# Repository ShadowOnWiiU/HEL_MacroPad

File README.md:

# HEL_MacroPad

## Macro Pad der 4AHEL Werkstaette

Current Look:

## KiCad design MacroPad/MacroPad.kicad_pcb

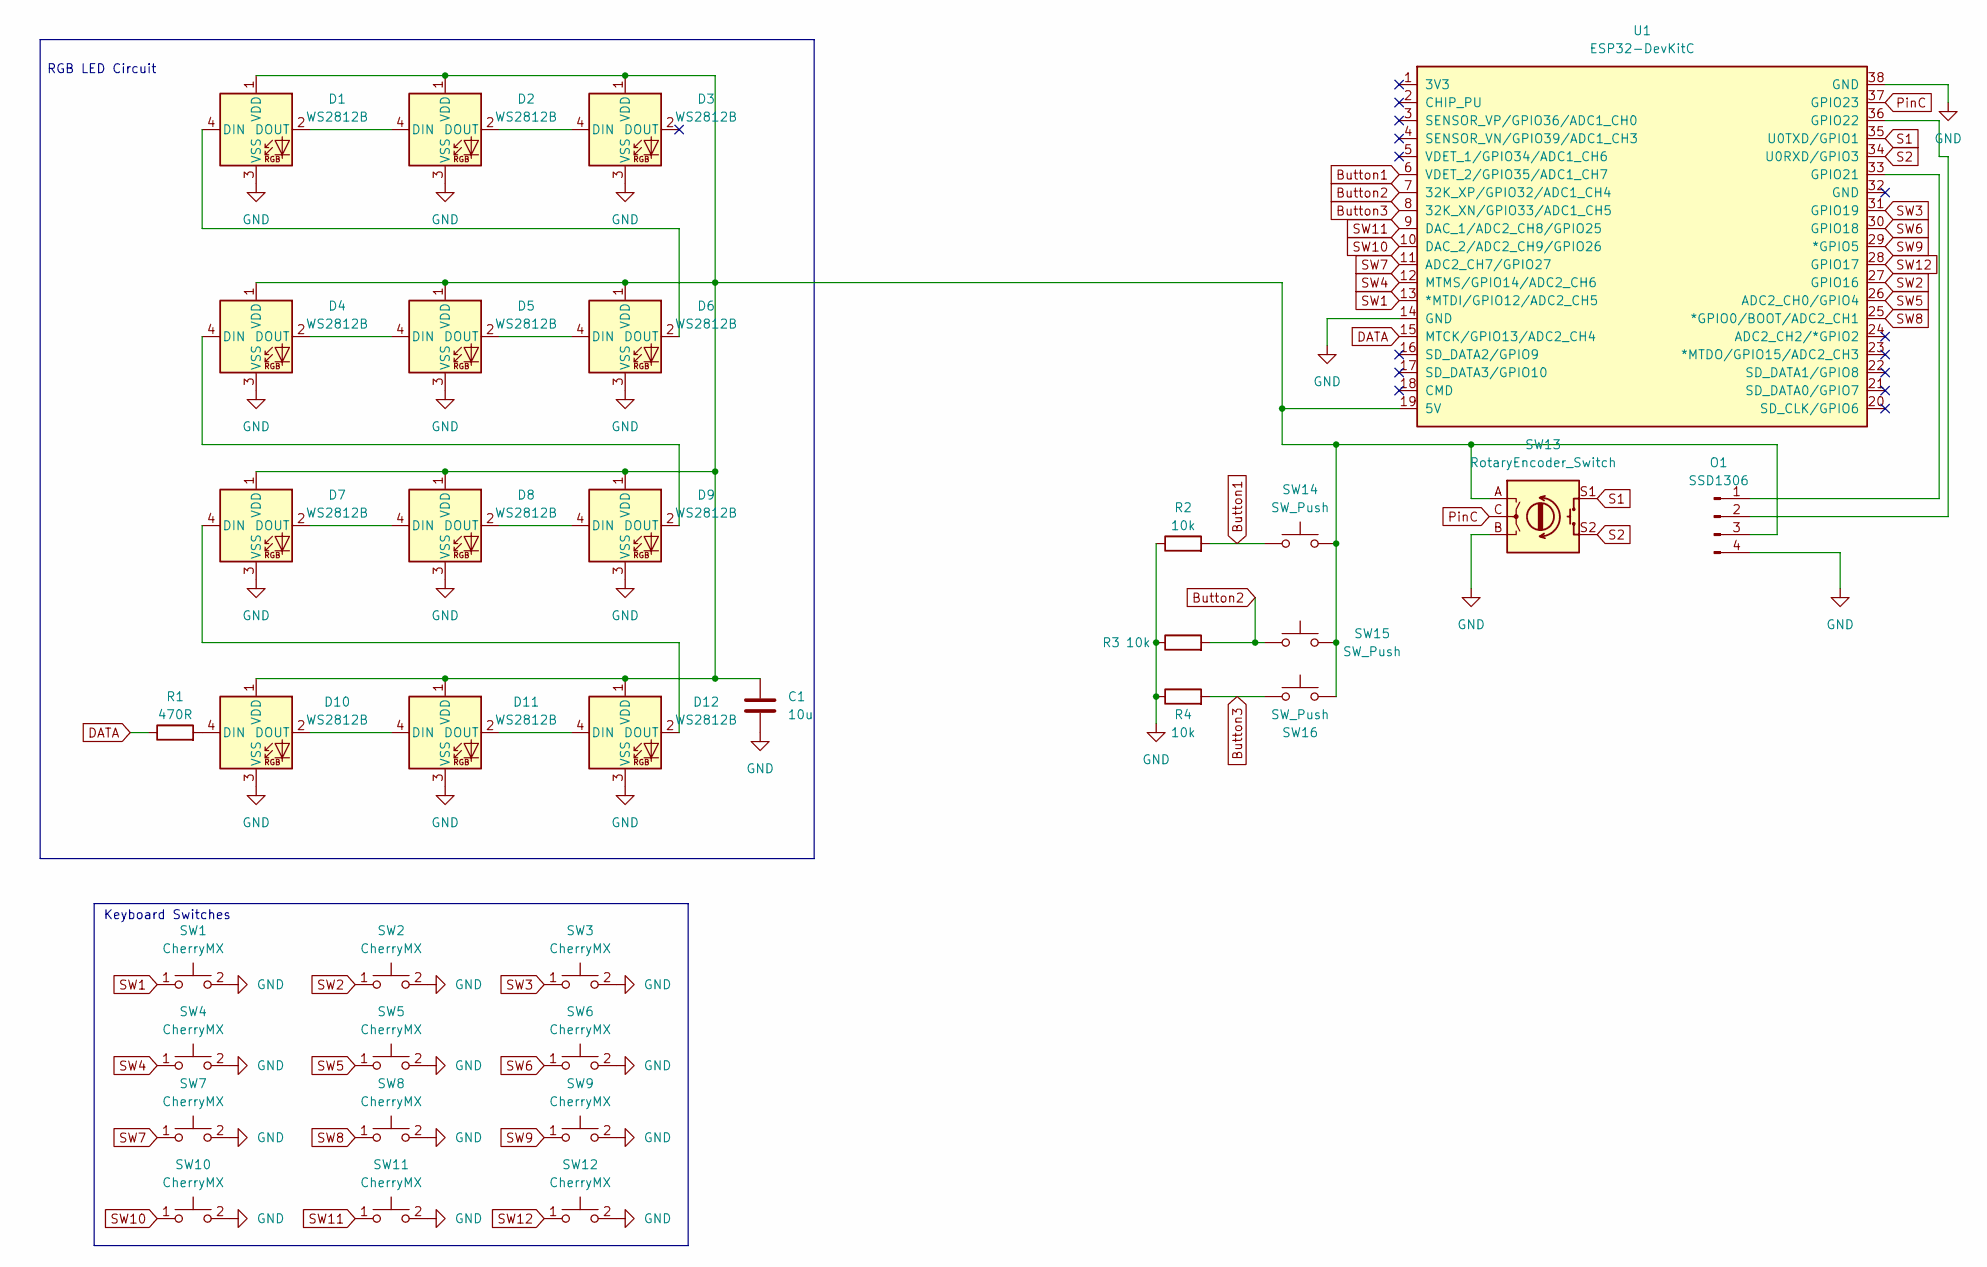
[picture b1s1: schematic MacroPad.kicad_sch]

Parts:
C1: 10u; C_1206_3216Metric_Pad1.33x1.80mm_HandSolder
D1, D2, D3, D4, D5, D6, D7, D8, D9, D10, D11, D12: WS2812B; LED_WS2812B_PLCC4_5.0x5.0mm_P3.2mm
O1: SSD1306; PinSocket_1x04_P2.54mm_Vertical
R1: 470R; R_1206_3216Metric_Pad1.30x1.75mm_HandSolder
R2, R3, R4: 10k; R_1206_3216Metric_Pad1.30x1.75mm_HandSolder
SW1, SW2, SW3, SW4, SW5, SW6, SW7, SW8, SW9, SW10, SW11, SW12: CherryMX; SW_Cherry_MX_Plate_1.00u
SW13: RotaryEncoder_Switch; RotaryEncoder_Alps_EC12E-Switch_Vertical_H20mm_CircularMoun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
SW14, SW15, SW16: SW_Push; SW_PUSH_6mm
U1: ESP32-DevKitC

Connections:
Button1: R2.2, SW14.1, U1.6 (VDET_2/GPIO35/ADC1_CH7)
Button2: R3.2, SW15.1, U1.7 (32K_XP/GPIO32/ADC1_CH4)
Button3: R4.2, SW16.1, U1.8 (32K_XN/GPIO33/ADC1_CH5)
DATA: R1.1, U1.15 (MTCK/GPIO13/ADC2_CH4)
GND: C1.2, D1.3 (VSS), D2.3 (VSS), D3.3 (VSS), D4.3 (VSS), D5.3 (VSS), D6.3 (VSS), D7.3 (VSS), D8.3 (VSS), D9.3 (VSS), D10.3 (VSS), D11.3 (VSS), D12.3 (VSS), O1.4, R2.1, R3.1, R4.1, SW1.2, SW2.2, SW3.2, SW4.2, SW5.2, SW6.2, SW7.2, SW8.2, SW9.2, SW10.2, SW11.2, SW12.2, SW13.B, U1.14 (GND), U1.38 (GND)
unnamed: C1.1, D1.1 (VDD), D2.1 (VDD), D3.1 (VDD), D4.1 (VDD), D5.1 (VDD), D6.1 (VDD), D7.1 (VDD), D8.1 (VDD), D9.1 (VDD), D10.1 (VDD), D11.1 (VDD), D12.1 (VDD), O1.3, SW13.A, SW14.2, SW15.2, SW16.2, U1.19 (5V)
unnamed: D1.2 (DOUT), D2.4 (DIN)
unnamed: D1.4 (DIN), D6.2 (DOUT)
unnamed: D2.2 (DOUT), D3.4 (DIN)
unnamed: D4.2 (DOUT), D5.4 (DIN)
unnamed: D4.4 (DIN), D9.2 (DOUT)
unnamed: D5.2 (DOUT), D6.4 (DIN)
unnamed: D7.2 (DOUT), D8.4 (DIN)
unnamed: D8.2 (DOUT), D9.4 (DIN)
unnamed: D10.2 (DOUT), D11.4 (DIN)
unnamed: D10.4 (DIN), R1.2
unnamed: D11.2 (DOUT), D12.4 (DIN)
unnamed: D7.4 (DIN), D12.2 (DOUT)
unnamed: O1.1, U1.33 (GPIO21)
unnamed: O1.2, U1.36 (GPIO22)
PinC: SW13.C, U1.37 (GPIO23)
S1: SW13.S1, U1.35 (U0TXD/GPIO1)
S2: SW13.S2, U1.34 (U0RXD/GPIO3)
SW1: SW1.1, U1.13 (*MTDI/GPIO12/ADC2_CH5)
SW2: SW2.1, U1.27 (GPIO16)
SW3: SW3.1, U1.31 (GPIO19)
SW4: SW4.1, U1.12 (MTMS/GPIO14/ADC2_CH6)
SW5: SW5.1, U1.26 (ADC2_CH0/GPIO4)
SW6: SW6.1, U1.30 (GPIO18)
SW7: SW7.1, U1.11 (ADC2_CH7/GPIO27)
SW8: SW8.1, U1.25 (*GPIO0/BOOT/ADC2_CH1)
SW9: SW9.1, U1.29 (*GPIO5)
SW10: SW10.1, U1.10 (DAC_2/ADC2_CH9/GPIO26)
SW11: SW11.1, U1.9 (DAC_1/ADC2_CH8/GPIO25)
SW12: SW12.1, U1.28 (GPIO17)

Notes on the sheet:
Keyboard Switches
RGB LED Circuit

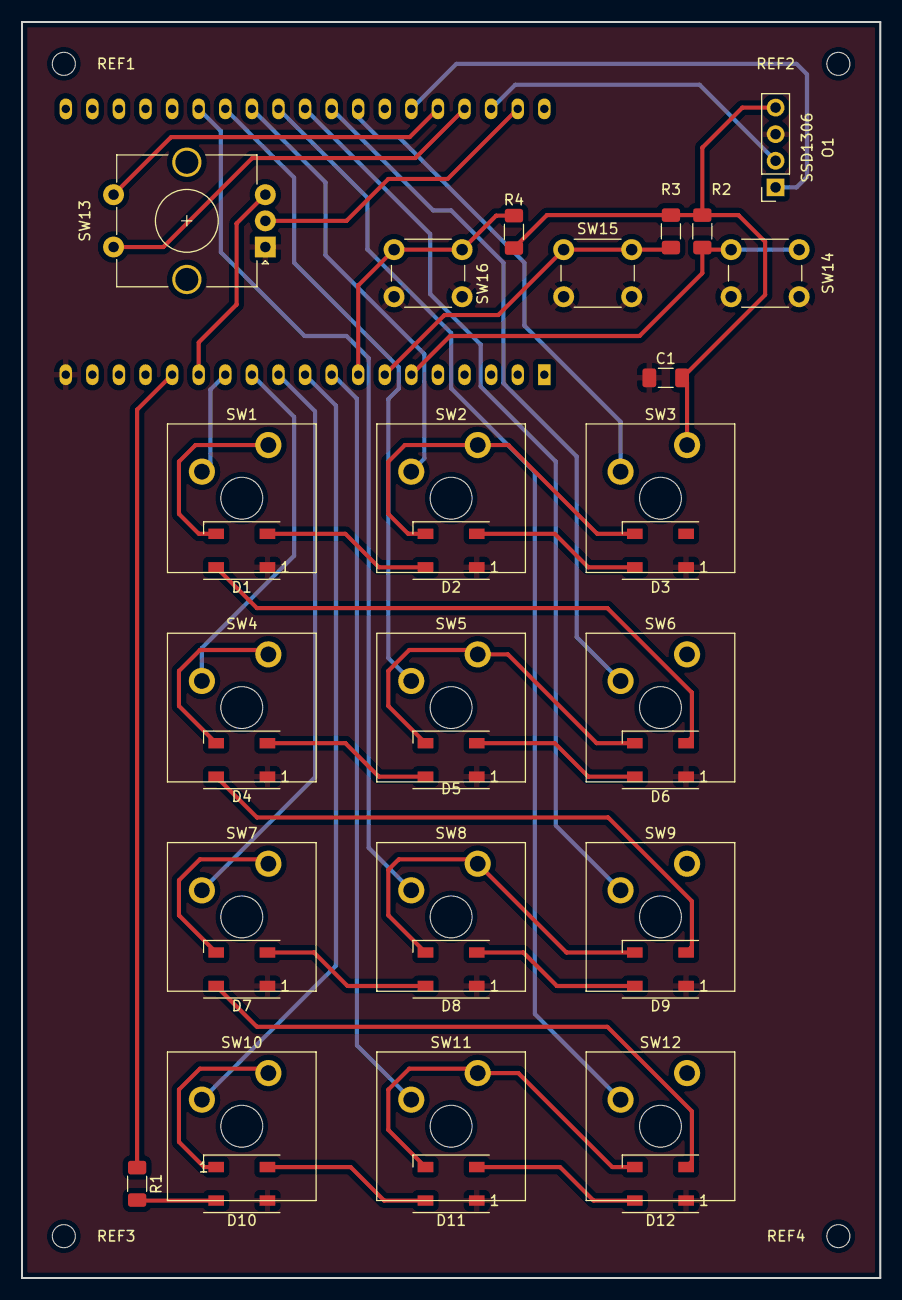
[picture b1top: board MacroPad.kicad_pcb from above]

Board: 2 copper layers, 82.0 x 120.0 mm, 39 parts (1 on the bottom side), 35 nets.

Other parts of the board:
REF1, REF2, REF3, REF4: MountingHole_2.2mm_M2

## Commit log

2022-12-15 RGB LED Circuit
2022-12-15 Amazon Links Added
2022-12-15 Links for Switches and Keycaps
2022-12-15 Switches Added to schematic
2022-12-15 forgot smth
2022-12-15 added capacitor to Keyboard Circuit to ground from Vin
2022-12-15 initial software
2022-12-15 initial PCB
2022-12-15 add platformio project
2022-12-15 Started PCB todo: ground and vin connections
2022-12-16 Finished PCB i think
2022-12-16 implement basic UI and threading
2022-12-21 Added Image of current PCB
2022-12-21 Updated PCB
2022-12-21 Added Image
2022-12-21 Added bottom and updated top view
2022-12-21 Update PCB
2022-12-21 Updated to match new PCB Layout
2022-12-21 updated PCB (esp at top now)
2022-12-21 Fixed formatting
2022-12-22 Updated Prices List
2022-12-22 Added new Prices and estimated Final Price
2022-12-25 updated materials list
2022-12-25 more accurate pricing
2022-12-26 redesign, added buttons and rotary encoder
2022-12-26 moved R1 into an aesthetically better position
2022-12-27 made zone filling a bit nicer (not shown in image yet)
2022-12-27 updated prices
2022-12-30 Fixed Issue #32 (price of buttons cause div/0)
2022-12-30 fixed position of R4 and GND connection
2023-01-11 updated pricing
2023-01-11 updated PCB to devkitC V2
2023-01-12 Plotted and Generated Drill and SVG files
2023-01-12 Added images locally
2023-01-12 Updated images
2023-01-12 updated drill and PDF files
2023-01-12 removed "outdated" warning
    since it is no longer outdated :p
2023-01-18 Updated Silkscreen
2023-01-22 added PCB costs
2023-01-22 minor updates
